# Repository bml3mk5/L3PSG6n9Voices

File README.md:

# PSG 6&9声カード for 日立ベーシックマスターレベル3

## フォルダ構成

    BackCover/ ..................... 背面カバーの3Dモデル
      L3BackSide2MJF-Resized.stl ... 背面カバーの3Dモデルファイル
      MegaZero2.0/ ................. Anycube MegaZero 2.0用
    Board/ ......................... 基板設計(KiCAD Version 5)
      main/ ........................ メイン基板
      side/ ........................ サブ基板(背面カバーに取り付ける基板)
      side_with_cover/ ............. 背面カバーを兼ねた基板

 * 3Dモデルから背面カバーを作ったときは、サブ基板を使用します。

-----
# PSG 6&9voices card for HITACHI BASIC MASTER LEVEL 3

## Folders:

    BackCover/ ..................... The 3D model of the back cover
      L3BackSide2MJF-Resized.stl ... The file of the back cover
      MegaZero2.0/ ................. For Anycube MegaZero 2.0
    Board/ ......................... Circuit board design(KiCAD Version 5)
      main/ ........................ The main board
      side/ ........................ The sub board (Attach to the back cover)
      side_with_cover/ ............. The side board which doubles as a back cover

 * When you made the back cover from 3D model, use the sub board.

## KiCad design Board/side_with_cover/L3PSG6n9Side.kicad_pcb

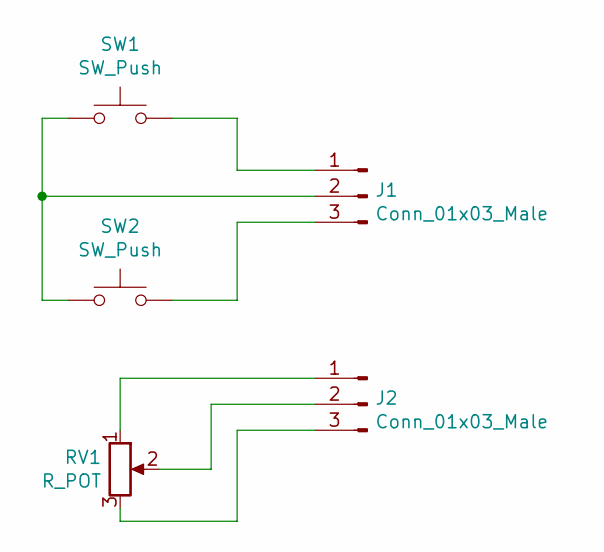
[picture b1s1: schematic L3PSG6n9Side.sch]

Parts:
J1, J2: Conn_01x03_Male; Pin_Header_Straight_1x03_Pitch2.54mm
RV1: R_POT; Potentiometer_Alps_RK09K_Horizontal
SW1, SW2: SW_Push; SW_PUSH_6mm

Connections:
unnamed: J1.1, SW1.2
unnamed: J1.2, SW1.1, SW2.1
unnamed: J1.3, SW2.2
unnamed: J2.1, RV1.1
unnamed: J2.2, RV1.2
unnamed: J2.3, RV1.3

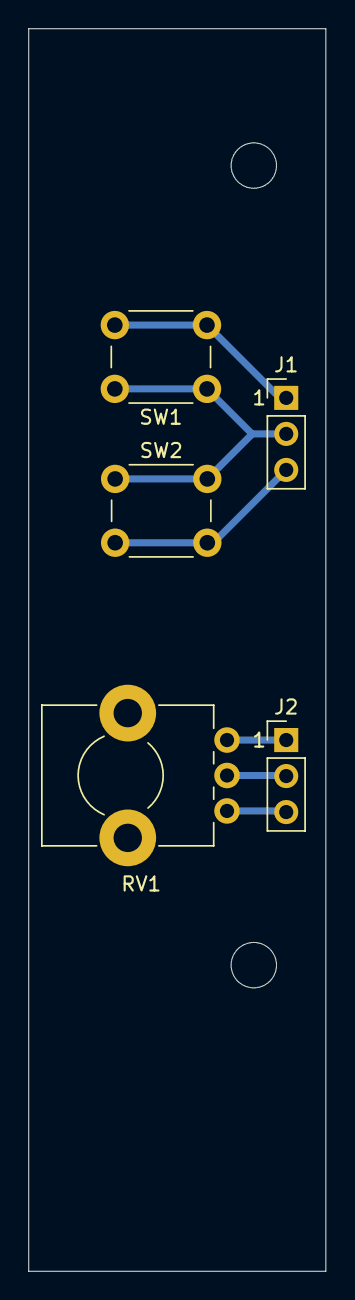
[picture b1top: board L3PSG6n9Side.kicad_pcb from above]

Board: 2 copper layers, 21.0 x 87.6 mm, 5 parts (0 on the bottom side), 6 nets.

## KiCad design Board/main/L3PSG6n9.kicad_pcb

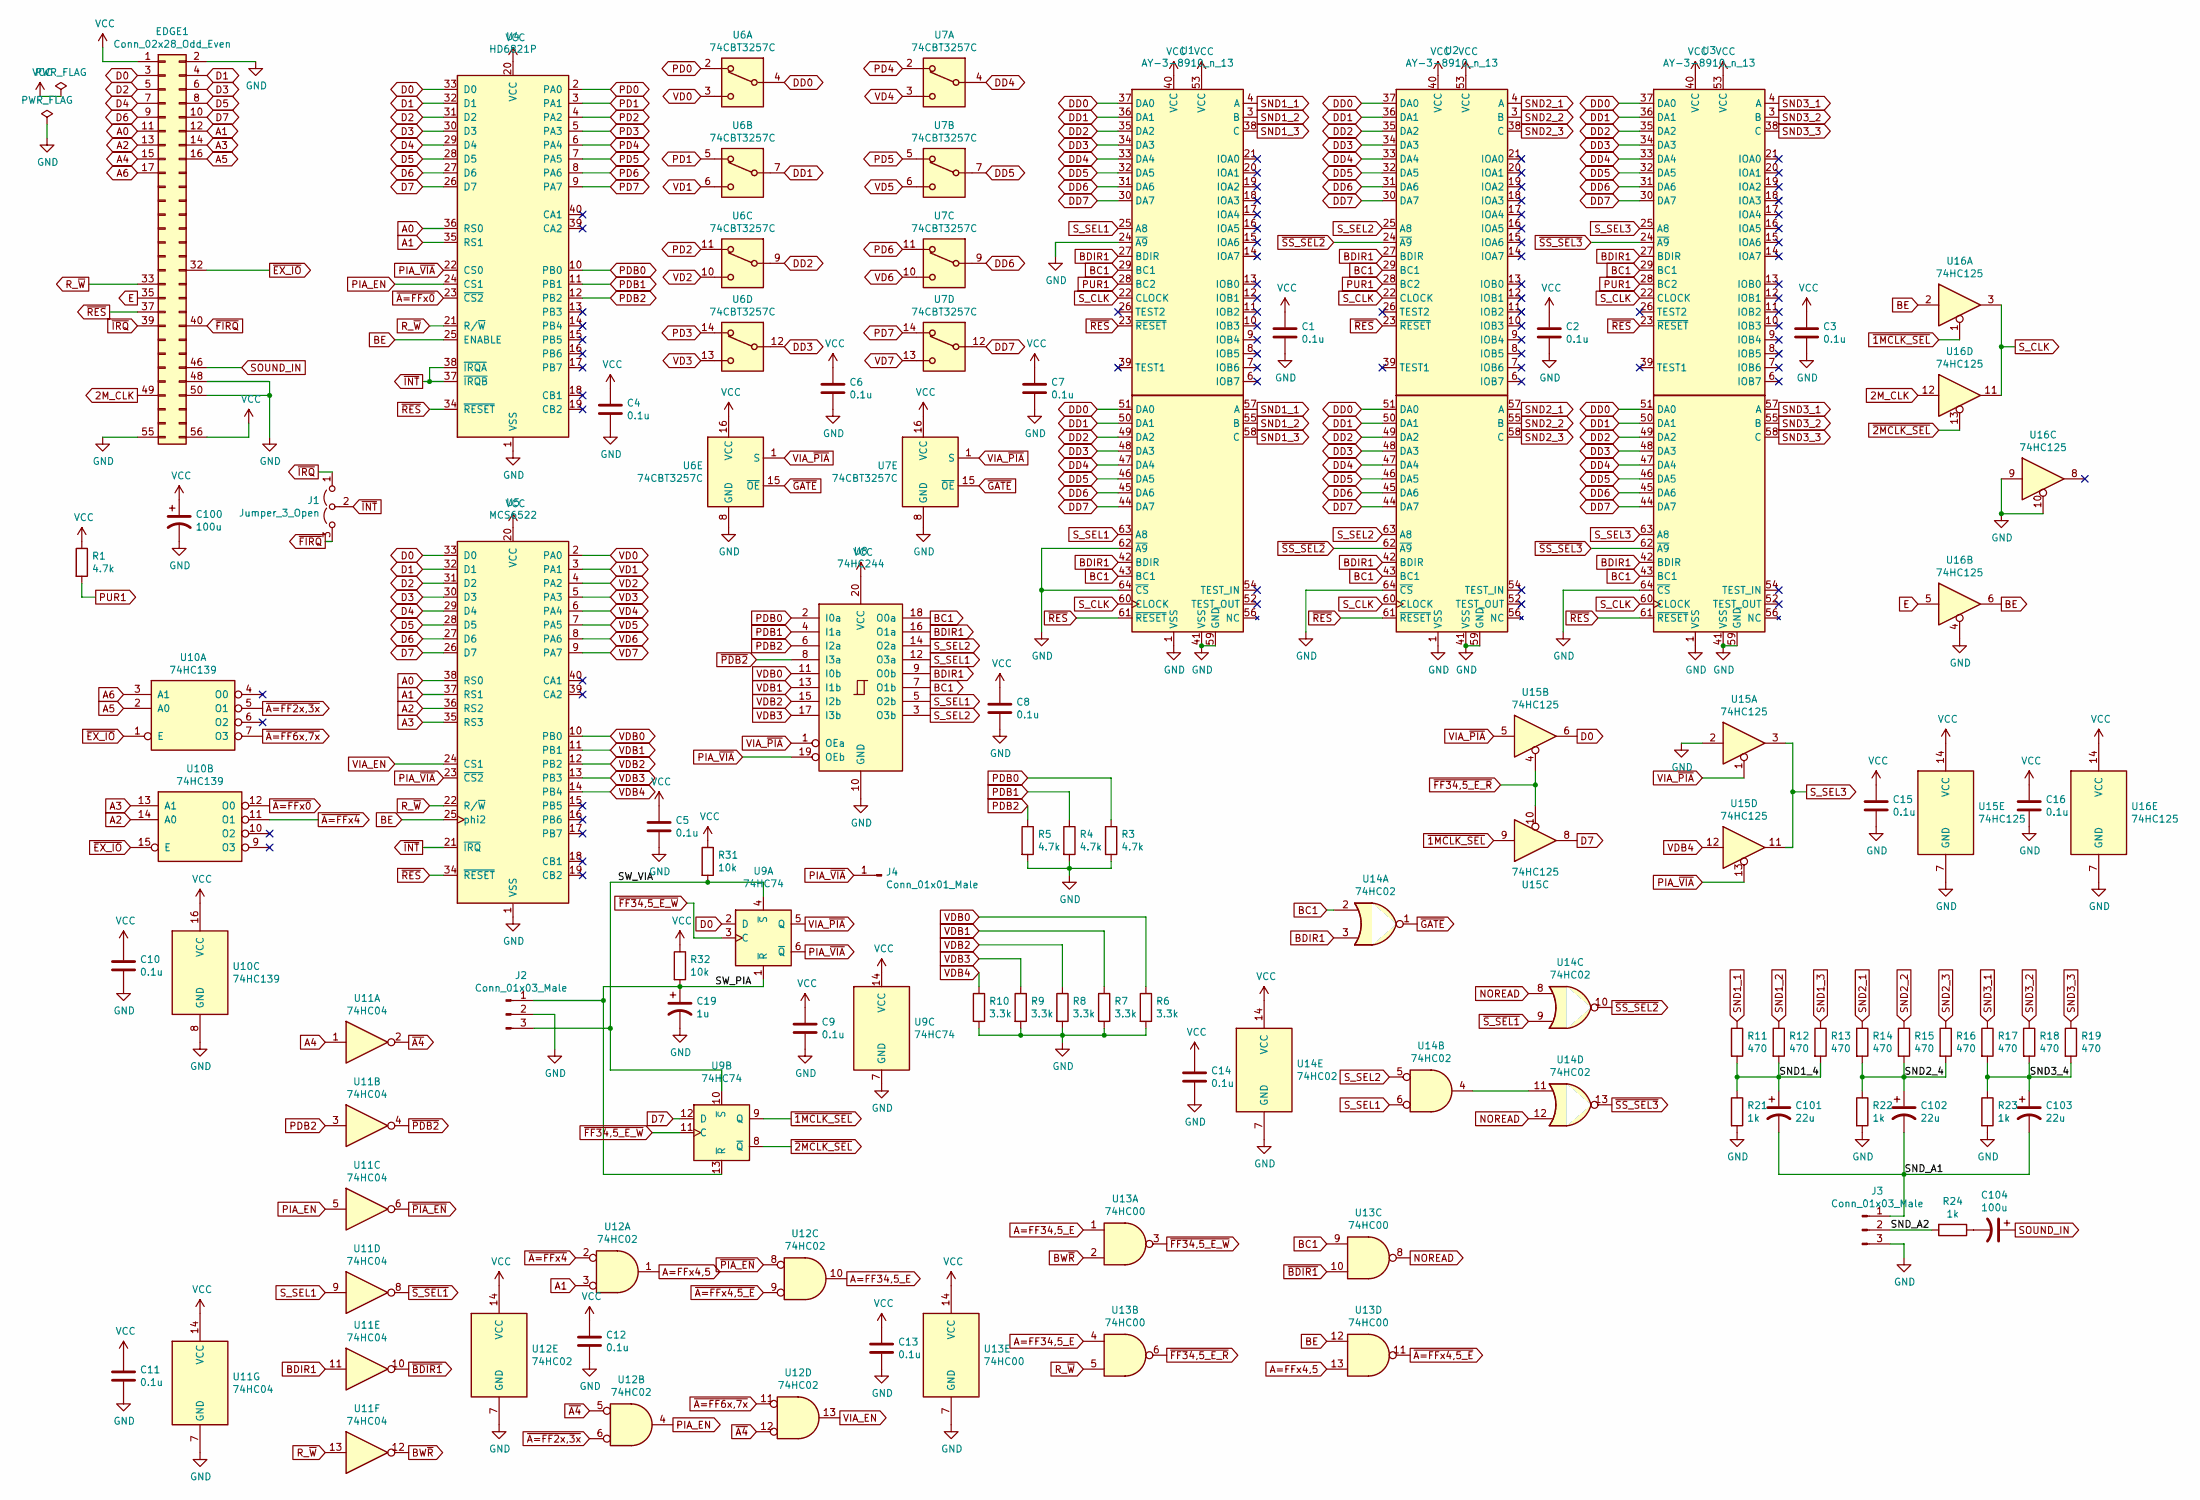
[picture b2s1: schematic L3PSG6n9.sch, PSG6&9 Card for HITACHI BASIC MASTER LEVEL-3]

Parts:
C1, C2, C3, C4, C5, C6, C7, C8, C9, C10, C11, C12, C13, C14, C15, C16: 0.1u; C_Disc_D3.0mm_W2.0mm_P2.50mm
C19: 1u; CP_Radial_D5.0mm_P2.50mm
C100: 100u; CP_Radial_D7.5mm_P2.50mm
C101, C102, C103: 22u; CP_Radial_D5.0mm_P2.50mm
C104: 100u; CP_Radial_D5.0mm_P2.50mm
EDGE1: Conn_02x28_Odd_Even; CardEdge56
J1: Jumper_3_Open; Pin_Header_Straight_1x03_Pitch2.54mm
J2, J3: Conn_01x03_Male; PINHEAD1-3
J4: Conn_01x01_Male; Pin_Header_Angled_1x01_Pitch2.54mm
R1, R3, R4, R5: 4.7k; R_Axial_DIN0207_L6.3mm_D2.5mm_P2.54mm_Vertical
R6, R7, R8, R9, R10: 3.3k; R_Axial_DIN0207_L6.3mm_D2.5mm_P2.54mm_Vertical
R11, R12, R13, R14, R15, R16, R17, R18, R19: 470; R_Axial_DIN0207_L6.3mm_D2.5mm_P2.54mm_Vertical
R21, R22, R23, R24: 1k; R_Axial_DIN0207_L6.3mm_D2.5mm_P2.54mm_Vertical
R31, R32: 10k; R_Axial_DIN0207_L6.3mm_D2.5mm_P2.54mm_Vertical
U1, U2, U3: AY-3-8910_n_13; DIP40n24
U4: HD6821P; DIP40
U5: MCS6522; DIP40
U6, U7: 74CBT3257C; SOIC-16
U8: 74HC244; SOIC-20
U9: 74HC74; SOIC-14
U10: 74HC139; SOIC-16
U11: 74HC04; SOIC-14
U12, U14: 74HC02; SOIC-14
U13: 74HC00; SOIC-14
U15, U16: 74HC125; SOIC-14

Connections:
2M_CLK: EDGE1.49, U16.12
/SND1_4: C101.1, R11.2, R12.2, R13.2, R21.1
/SND2_4: C102.1, R14.2, R15.2, R16.2, R22.1
/SND3_4: C103.1, R17.2, R18.2, R19.2, R23.1
/SND_A1: C101.2, C102.2, C103.2, J3.1
/SND_A2: J3.2, R24.2
/SW_PIA: C19.1, J2.1, R32.2, U9.1 (~R), U9.13 (~R)
/SW_VIA: J2.3, R31.2, U9.4 (~S), U9.10 (~S)
A0: EDGE1.11, U4.36 (RS0), U5.38 (RS0)
A1: EDGE1.12, U4.35 (RS1), U5.37 (RS1), U12.3
A2: EDGE1.13, U5.36 (RS2), U10.14 (A0)
A3: EDGE1.14, U5.35 (RS3), U10.13 (A1)
A4: EDGE1.15, U11.1
A5: EDGE1.16, U10.2 (A0)
A6: EDGE1.17, U10.3 (A1)
A=FF34,5_E: U12.10, U13.1, U13.4
A=FFx4,5: U12.1, U13.13
BC1: U1.29 (BC1), U1.43 (BC1), U2.29 (BC1), U2.43 (BC1), U3.29 (BC1), U3.43 (BC1), U8.7 (O1b), U8.18 (O0a), U13.9, U14.2
BDIR1: U1.27 (BDIR), U1.42 (BDIR), U2.27 (BDIR), U2.42 (BDIR), U3.27 (BDIR), U3.42 (BDIR), U8.9 (O0b), U8.16 (O1a), U11.11, U14.3
BE: U4.25 (ENABLE), U5.25 (phi2), U13.12, U16.2, U16.6
BW~R: U11.12, U13.2
D0: EDGE1.3, U4.33 (D0), U5.33 (D0), U9.2 (D), U15.6
D1: EDGE1.4, U4.32 (D1), U5.32 (D1)
D2: EDGE1.5, U4.31 (D2), U5.31 (D2)
D3: EDGE1.6, U4.30 (D3), U5.30 (D3)
D4: EDGE1.7, U4.29 (D4), U5.29 (D4)
D5: EDGE1.8, U4.28 (D5), U5.28 (D5)
D6: EDGE1.9, U4.27 (D6), U5.27 (D6)
D7: EDGE1.10, U4.26 (D7), U5.26 (D7), U9.12 (D), U15.8
DD0: U1.37 (DA0), U1.51 (DA0), U2.37 (DA0), U2.51 (DA0), U3.37 (DA0), U3.51 (DA0), U6.4
DD1: U1.36 (DA1), U1.50 (DA1), U2.36 (DA1), U2.50 (DA1), U3.36 (DA1), U3.50 (DA1), U6.7
DD2: U1.35 (DA2), U1.49 (DA2), U2.35 (DA2), U2.49 (DA2), U3.35 (DA2), U3.49 (DA2), U6.9
DD3: U1.34 (DA3), U1.48 (DA3), U2.34 (DA3), U2.48 (DA3), U3.34 (DA3), U3.48 (DA3), U6.12
DD4: U1.33 (DA4), U1.47 (DA4), U2.33 (DA4), U2.47 (DA4), U3.33 (DA4), U3.47 (DA4), U7.4
DD5: U1.32 (DA5), U1.46 (DA5), U2.32 (DA5), U2.46 (DA5), U3.32 (DA5), U3.46 (DA5), U7.7
DD6: U1.31 (DA6), U1.45 (DA6), U2.31 (DA6), U2.45 (DA6), U3.31 (DA6), U3.45 (DA6), U7.9
DD7: U1.30 (DA7), U1.44 (DA7), U2.30 (DA7), U2.44 (DA7), U3.30 (DA7), U3.44 (DA7), U7.12
E: EDGE1.35, U16.5
GND: C1.2, C2.2, C3.2, C4.2, C5.2, C6.2, C7.2, C8.2, C9.2, C10.2, C11.2, C12.2, C13.2, C14.2, C15.2, C16.2, C19.2, C100.2, EDGE1.2, EDGE1.48, EDGE1.50, EDGE1.55, J2.2, J3.3, R3.2, R4.2, R5.2, R6.2, R7.2, R8.2, R9.2, R10.2, R21.2, R22.2, R23.2, U1.1 (VSS), U1.24 (~A9), U1.41 (VSS), U1.59 (GND), U1.62 (~A9), U1.64 (~CS), U2.1 (VSS), U2.41 (VSS), U2.59 (GND), U2.64 (~CS), U3.1 (VSS), U3.41 (VSS), U3.59 (GND), U3.64 (~CS), U4.1 (VSS), U5.1 (VSS), U6.8 (GND), U7.8 (GND), U8.10 (GND), U9.7 (GND), U10.8 (GND), U11.7 (GND), U12.7 (GND), U13.7 (GND), U14.7 (GND), U15.2, U15.7 (GND), U16.4, U16.7 (GND), U16.9, U16.10
NOREAD: U13.8, U14.8, U14.12
unnamed: C104.2, R24.1
unnamed: U14.4, U14.11
PD0: U4.2 (PA0), U6.2
PD1: U4.3 (PA1), U6.5
PD2: U4.4 (PA2), U6.11
PD3: U4.5 (PA3), U6.14
PD4: U4.6 (PA4), U7.2
PD5: U4.7 (PA5), U7.5
PD6: U4.8 (PA6), U7.11
PD7: U4.9 (PA7), U7.14
PDB0: R3.1, U4.10 (PB0), U8.2 (I0a)
PDB1: R4.1, U4.11 (PB1), U8.4 (I1a)
PDB2: R5.1, U4.12 (PB2), U8.6 (I2a), U11.3
PIA_EN: U4.24 (CS1), U11.5, U12.4
PIA_~VIA: J4.1, U4.22 (CS0), U5.23 (~CS2), U8.19 (OEb), U9.6 (~Q), U15.13
PUR1: R1.2, U1.28 (BC2), U2.28 (BC2), U3.28 (BC2)
R_~W: EDGE1.33, U4.21 (R/~W), U5.22 (R/~W), U11.13, U13.5
SND1_1: R11.1, U1.4 (A), U1.57 (A)
SND1_2: R12.1, U1.3 (B), U1.55 (B)
SND1_3: R13.1, U1.38 (C), U1.58 (C)
SND2_1: R14.1, U2.4 (A), U2.57 (A)
SND2_2: R15.1, U2.3 (B), U2.55 (B)
SND2_3: R16.1, U2.38 (C), U2.58 (C)
SND3_1: R17.1, U3.4 (A), U3.57 (A)
SND3_2: R18.1, U3.3 (B), U3.55 (B)
SND3_3: R19.1, U3.38 (C), U3.58 (C)
SOUND_IN: C104.1, EDGE1.46
S_CLK: U1.22 (CLOCK), U1.60 (CLOCK), U2.22 (CLOCK), U2.60 (CLOCK), U3.22 (CLOCK), U3.60 (CLOCK), U16.3, U16.11
S_SEL1: U1.25 (A8), U1.63 (A8), U8.5 (O2b), U8.12 (O3a), U11.9, U14.6
S_SEL2: U2.25 (A8), U2.63 (A8), U8.3 (O3b), U8.14 (O2a), U14.5
S_SEL3: U3.25 (A8), U3.63 (A8), U15.3, U15.11
VCC: C1.1, C2.1, C3.1, C4.1, C5.1, C6.1, C7.1, C8.1, C9.1, C10.1, C11.1, C12.1, C13.1, C14.1, C15.1, C16.1, C100.1, EDGE1.1, EDGE1.56, R1.1, R31.1, R32.1, U1.40 (VCC), U1.53 (VCC), U2.40 (VCC), U2.53 (VCC), U3.40 (VCC), U3.53 (VCC), U4.20 (VCC), U5.20 (VCC), U6.16 (VCC), U7.16 (VCC), U8.20 (VCC), U9.14 (VCC), U10.16 (VCC), U11.14 (VCC), U12.14 (VCC), U13.14 (VCC), U14.14 (VCC), U15.14 (VCC), U16.14 (VCC)
VD0: U5.2 (PA0), U6.3
VD1: U5.3 (PA1), U6.6
VD2: U5.4 (PA2), U6.10
VD3: U5.5 (PA3), U6.13
VD4: U5.6 (PA4), U7.3
VD5: U5.7 (PA5), U7.6
VD6: U5.8 (PA6), U7.10
VD7: U5.9 (PA7), U7.13
VDB0: R6.1, U5.10 (PB0), U8.11 (I0b)
VDB1: R7.1, U5.11 (PB1), U8.13 (I1b)
VDB2: R8.1, U5.12 (PB2), U8.15 (I2b)
VDB3: R9.1, U5.13 (PB3), U8.17 (I3b)
VDB4: R10.1, U5.14 (PB4), U15.12
VIA_EN: U5.24 (CS1), U12.13
VIA_~PIA: U6.1 (S), U7.1 (S), U8.1 (OEa), U9.5 (Q), U15.1, U15.5
~1MCLK_SEL: U9.9 (Q), U15.9, U16.1
~2MCLK_SEL: U9.8 (~Q), U16.13
~A4: U11.2, U12.5, U12.12
~A=FF2x,3x: U10.5 (O1), U12.6
~A=FF6x,7x: U10.7 (O3), U12.11
~A=FFx0: U4.23 (~CS2), U10.12 (O0)
~A=FFx4: U10.11 (O1), U12.2
~A=FFx4,5_E: U12.9, U13.11
~BDIR1: U11.10, U13.10
~EX_IO: EDGE1.32, U10.1 (E), U10.15 (E)
~FF34,5_E_R: U13.6, U15.4, U15.10
~FF34,5_E_W: U9.3 (C), U9.11 (C), U13.3
~FIRQ: EDGE1.40, J1.3 (B)
~GATE: U6.15 (~OE), U7.15 (~OE), U14.1
~INT: J1.2 (C), U4.37 (~IRQB), U4.38 (~IRQA), U5.21 (~IRQ)
~IRQ: EDGE1.39, J1.1 (A)
~PDB2: U8.8 (I3a), U11.4
~PIA_EN: U11.6, U12.8
~RES: EDGE1.37, U1.23 (~RESET), U1.61 (~RESET), U2.23 (~RESET), U2.61 (~RESET), U3.23 (~RESET), U3.61 (~RESET), U4.34 (~RESET), U5.34 (~RESET)
~SS_SEL2: U2.24 (~A9), U2.62 (~A9), U14.10
~SS_SEL3: U3.24 (~A9), U3.62 (~A9), U14.13
~S_SEL1: U11.8, U14.9

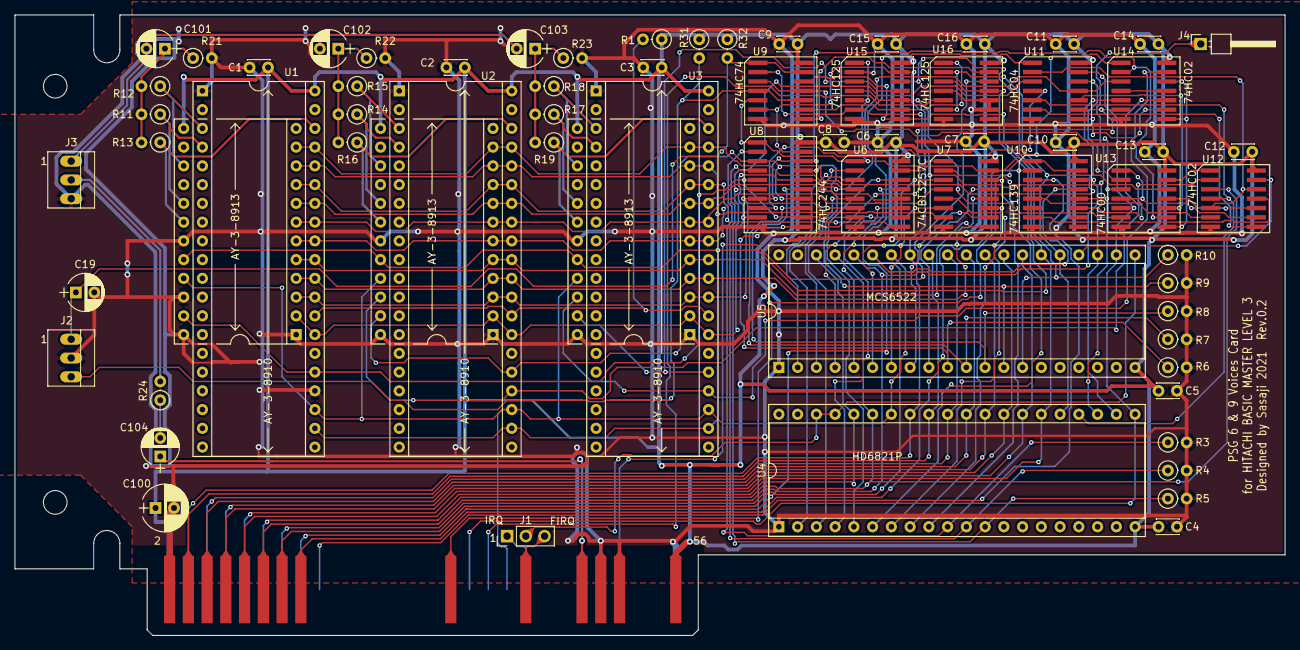
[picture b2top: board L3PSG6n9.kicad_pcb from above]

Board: 2 copper layers, 172.1 x 84.1 mm, 68 parts (0 on the bottom side), 109 nets.

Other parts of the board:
T: T

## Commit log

2023-03-11 Revision 0.2
2023-11-19 Add a image
2023-11-20 Modify documents
2023-11-27 Add documents
